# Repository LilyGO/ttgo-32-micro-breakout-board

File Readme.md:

## TTGO 32 MICRO Breakout Board

A Breakoutboard for the TTGO 32 MICRO made with KiCAD 

Follow me on Instagram for more Projects: [https://instagram.com/pauls_3d_things](https://instagram.com/pauls_3d_things)

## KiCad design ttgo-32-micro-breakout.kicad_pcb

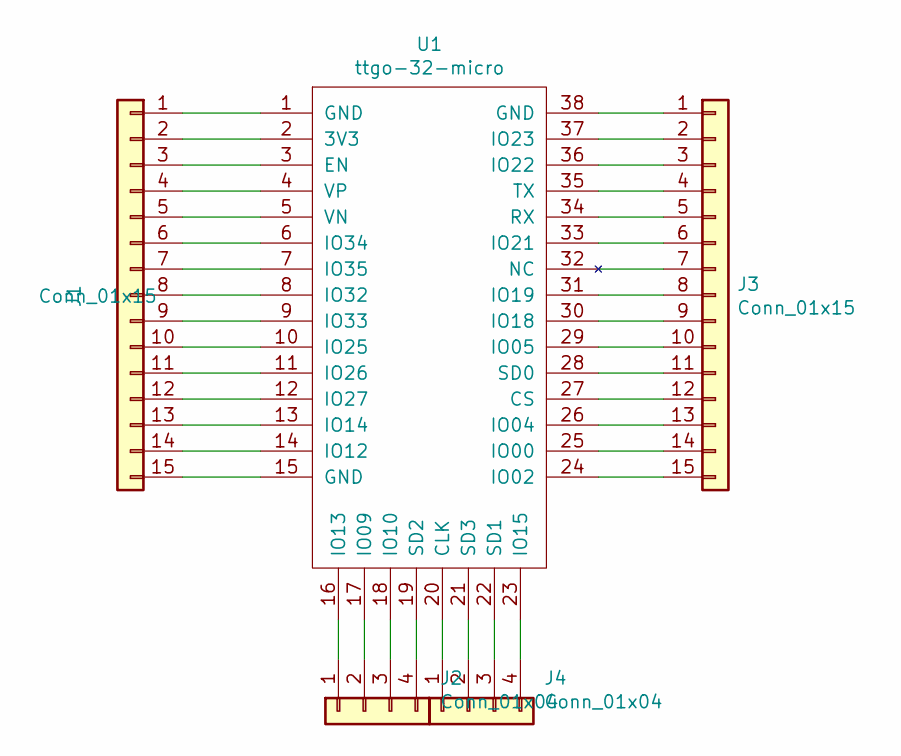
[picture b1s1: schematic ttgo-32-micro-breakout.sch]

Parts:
J1, J3: Conn_01x15; PinHeader_1x15_P2.54mm_Vertical
J2, J4: Conn_01x04; PinHeader_1x04_P2.54mm_Vertical
U1: ttgo-32-micro

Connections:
unnamed: J1.1, U1.1 (GND)
unnamed: J1.2, U1.2 (3V3)
unnamed: J1.3, U1.3 (EN)
unnamed: J1.4, U1.4 (VP)
unnamed: J1.5, U1.5 (VN)
unnamed: J1.6, U1.6 (IO34)
unnamed: J1.7, U1.7 (IO35)
unnamed: J1.8, U1.8 (IO32)
unnamed: J1.9, U1.9 (IO33)
unnamed: J1.10, U1.10 (IO25)
unnamed: J1.11, U1.11 (IO26)
unnamed: J1.12, U1.12 (IO27)
unnamed: J1.13, U1.13 (IO14)
unnamed: J1.14, U1.14 (IO12)
unnamed: J1.15, U1.15 (GND)
unnamed: J2.1, U1.16 (IO13)
unnamed: J2.2, U1.17 (IO09)
unnamed: J2.3, U1.18 (IO10)
unnamed: J2.4, U1.19 (SD2)
unnamed: J3.1, U1.38 (GND)
unnamed: J3.2, U1.37 (IO23)
unnamed: J3.3, U1.36 (IO22)
unnamed: J3.4, U1.35 (TX)
unnamed: J3.5, U1.34 (RX)
unnamed: J3.6, U1.33 (IO21)
unnamed: J3.7, U1.32 (NC)
unnamed: J3.8, U1.31 (IO19)
unnamed: J3.9, U1.30 (IO18)
unnamed: J3.10, U1.29 (IO05)
unnamed: J3.11, U1.28 (SD0)
unnamed: J3.12, U1.27 (CS)
unnamed: J3.13, U1.26 (IO04)
unnamed: J3.14, U1.25 (IO00)
unnamed: J3.15, U1.24 (IO02)
unnamed: J4.1, U1.20 (CLK)
unnamed: J4.2, U1.21 (SD3)
unnamed: J4.3, U1.22 (SD1)
unnamed: J4.4, U1.23 (IO15)

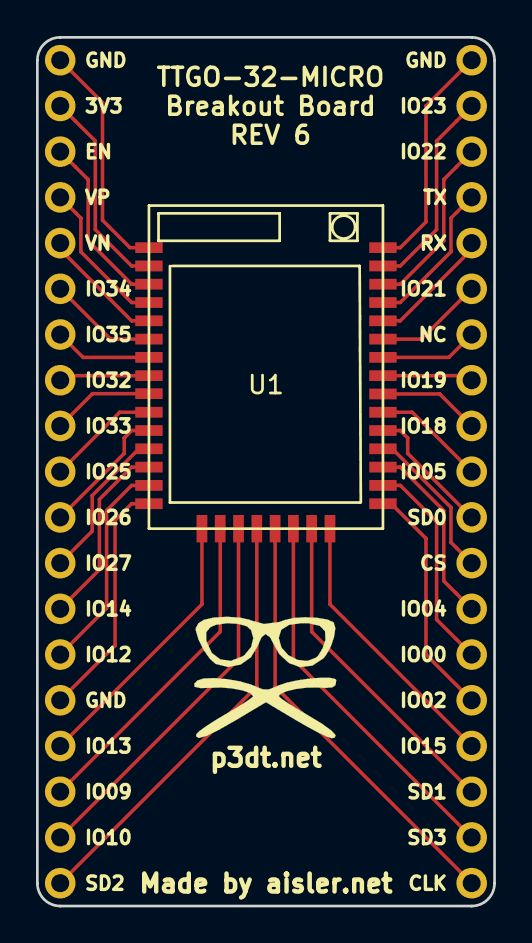
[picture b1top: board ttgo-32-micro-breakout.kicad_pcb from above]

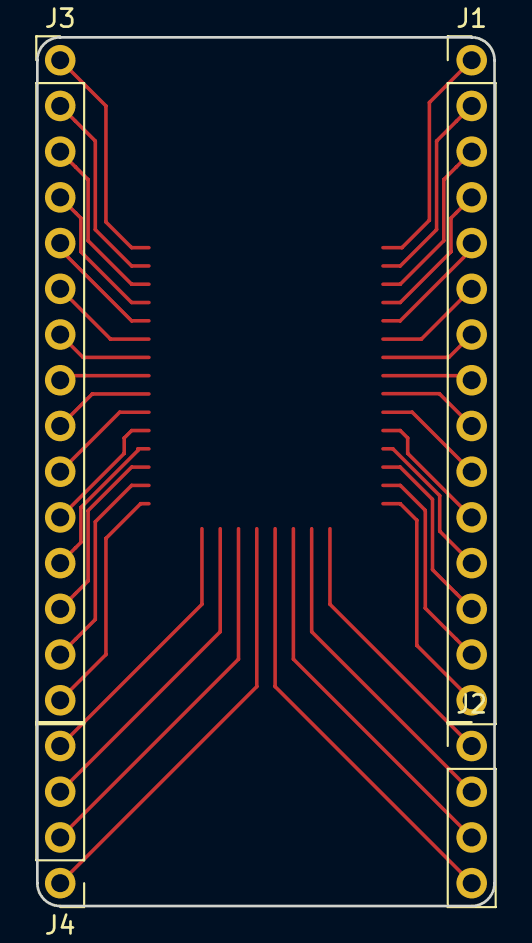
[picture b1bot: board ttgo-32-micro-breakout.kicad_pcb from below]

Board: 2 copper layers, 25.4 x 48.3 mm, 5 parts (4 on the bottom side), 38 nets.

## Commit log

2019-05-23 add readme
2019-05-23 add license
